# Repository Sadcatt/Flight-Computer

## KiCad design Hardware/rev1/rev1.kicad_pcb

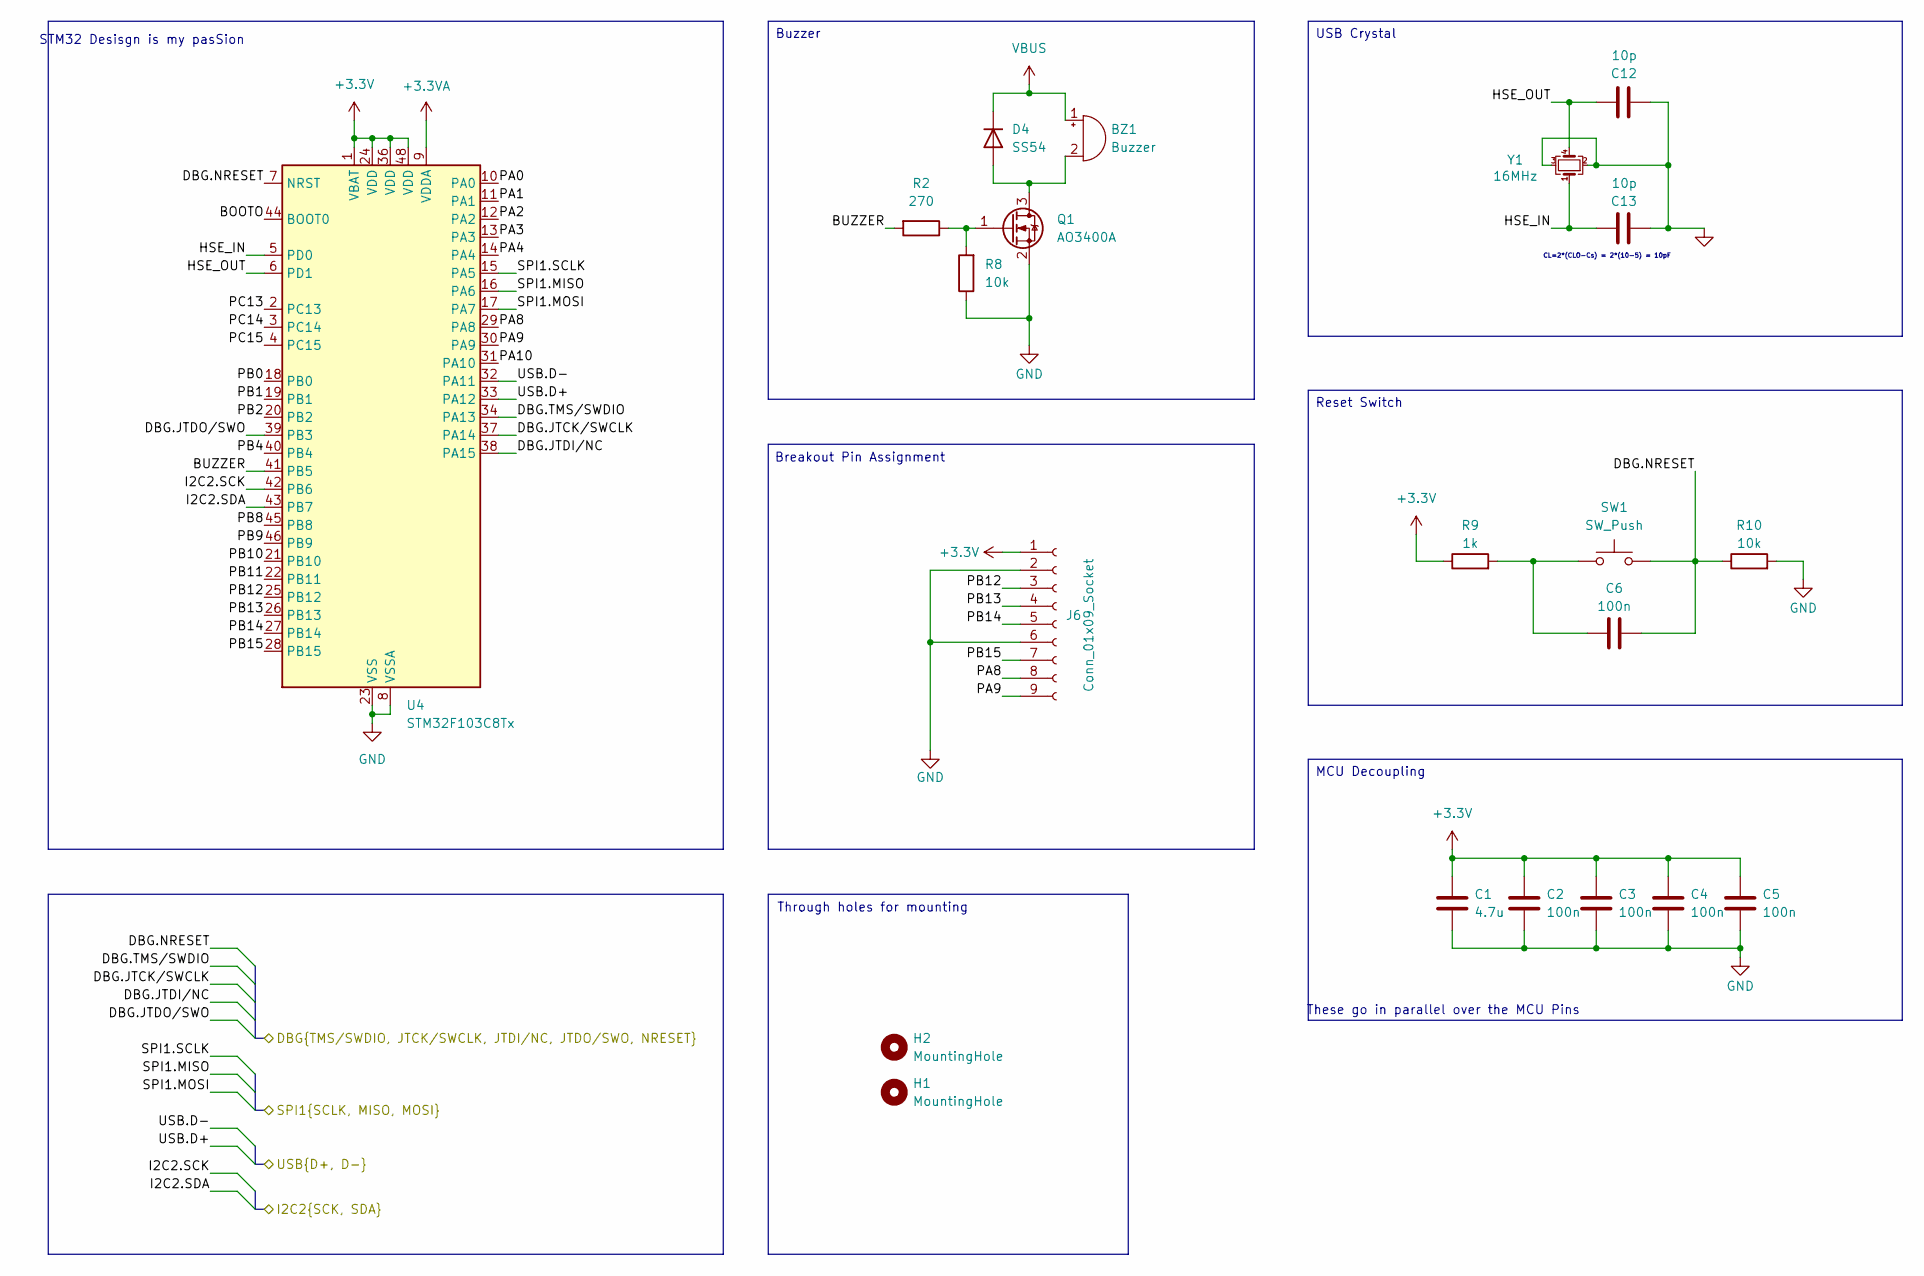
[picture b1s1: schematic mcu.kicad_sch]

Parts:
BZ1: Buzzer; MagneticBuzzer_Kingstate_KCG0601
C1: 4.7u; C_0603_1608Metric
C2, C3, C4, C5, C6: 100n; C_0402_1005Metric
C12, C13: 10p; C_0402_1005Metric
D4: SS54; D_SMA; JLCPCB Part # C22452
H1, H2: MountingHole; MountingHole_3.2mm_M3
J6: Conn_01x09_Socket; PinHeader_1x09_P1.00mm_Vertical
Q1: AO3400A; SOT-23
R2: 270; R_0603_1608Metric
R8, R10: 10k; R_0603_1608Metric
R9: 1k; R_0603_1608Metric
SW1: SW_Push; SW_Push_1P1T_XKB_TS-1187A
U4: STM32F103C8Tx; LQFP-48_7x7mm_P0.5mm
Y1: 16MHz; Crystal_SMD_3225-4Pin_3.2x2.5mm

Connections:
+3.3V: C1.1, C2.1, C3.1, C4.1, C5.1, J6.1, R9.1, U4.1 (VBAT), U4.24 (VDD), U4.36 (VDD), U4.48 (VDD); also elsewhere on the board
+3.3VA: U4.9 (VDDA); also elsewhere on the board
/Microcontroller/BOOTO: U4.44 (BOOT0)
/Microcontroller/BUZZER: R2.2, U4.41 (PB5)
/Microcontroller/DBG.JTCK/SWCLK: U4.37 (PA14); also elsewhere on the board
/Microcontroller/DBG.JTDI/NC: U4.38 (PA15); also elsewhere on the board
/Microcontroller/DBG.JTDO/SWO: U4.39 (PB3); also elsewhere on the board
/Microcontroller/DBG.NRESET: C6.2, R10.1, SW1.2, U4.7 (NRST); also elsewhere on the board
/Microcontroller/DBG.TMS/SWDIO: U4.34 (PA13); also elsewhere on the board
/Microcontroller/HSE_IN: C13.1, U4.5 (PD0), Y1.1
/Microcontroller/HSE_OUT: C12.1, U4.6 (PD1), Y1.4
/Microcontroller/I2C2.SCK: U4.42 (PB6); also elsewhere on the board
/Microcontroller/I2C2.SDA: U4.43 (PB7); also elsewhere on the board
/Microcontroller/PA0: U4.10 (PA0)
/Microcontroller/PA1: U4.11 (PA1)
/Microcontroller/PA2: U4.12 (PA2)
/Microcontroller/PA3: U4.13 (PA3)
/Microcontroller/PA4: U4.14 (PA4)
/Microcontroller/PA8: J6.8, U4.29 (PA8)
/Microcontroller/PA9: J6.9, U4.30 (PA9)
/Microcontroller/PA10: U4.31 (PA10)
/Microcontroller/PB0: U4.18 (PB0)
/Microcontroller/PB1: U4.19 (PB1)
/Microcontroller/PB2: U4.20 (PB2)
/Microcontroller/PB4: U4.40 (PB4)
/Microcontroller/PB8: U4.45 (PB8)
/Microcontroller/PB9: U4.46 (PB9)
/Microcontroller/PB10: U4.21 (PB10)
/Microcontroller/PB11: U4.22 (PB11)
/Microcontroller/PB12: J6.3, U4.25 (PB12)
/Microcontroller/PB13: J6.4, U4.26 (PB13)
/Microcontroller/PB14: J6.5, U4.27 (PB14)
/Microcontroller/PB15: J6.7, U4.28 (PB15)
/Microcontroller/PC13: U4.2 (PC13)
/Microcontroller/PC14: U4.3 (PC14)
/Microcontroller/PC15: U4.4 (PC15)
/Microcontroller/SPI1.MISO: U4.16 (PA6); also elsewhere on the board
/Microcontroller/SPI1.MOSI: U4.17 (PA7); also elsewhere on the board
/Microcontroller/SPI1.SCLK: U4.15 (PA5); also elsewhere on the board
/Microcontroller/USB.D+: U4.33 (PA12); also elsewhere on the board
/Microcontroller/USB.D-: U4.32 (PA11); also elsewhere on the board
GND: C1.2, C2.2, C3.2, C4.2, C5.2, C12.2, C13.2, J6.2, J6.6, Q1.2 (S), R8.1, R10.2, U4.8 (VSSA), U4.23 (VSS), U4.35 (VSS), U4.47 (VSS), Y1.2, Y1.3; also elsewhere on the board
unnamed: BZ1.2 (-), D4.2 (A), Q1.3 (D)
unnamed: C6.1, R9.2, SW1.1
unnamed: Q1.1 (G), R2.1, R8.2
VBUS: BZ1.1 (+), D4.1 (K); also elsewhere on the board

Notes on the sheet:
Breakout Pin Assignment
These go in parallel over the MCU Pins
CL=2*(CLO-Cs) = 2*(10-5) = 10pF
STM32 Desisgn is my pasSion
Through holes for mounting
MCU Decoupling
USB Crystal
Reset Switch
Buzzer

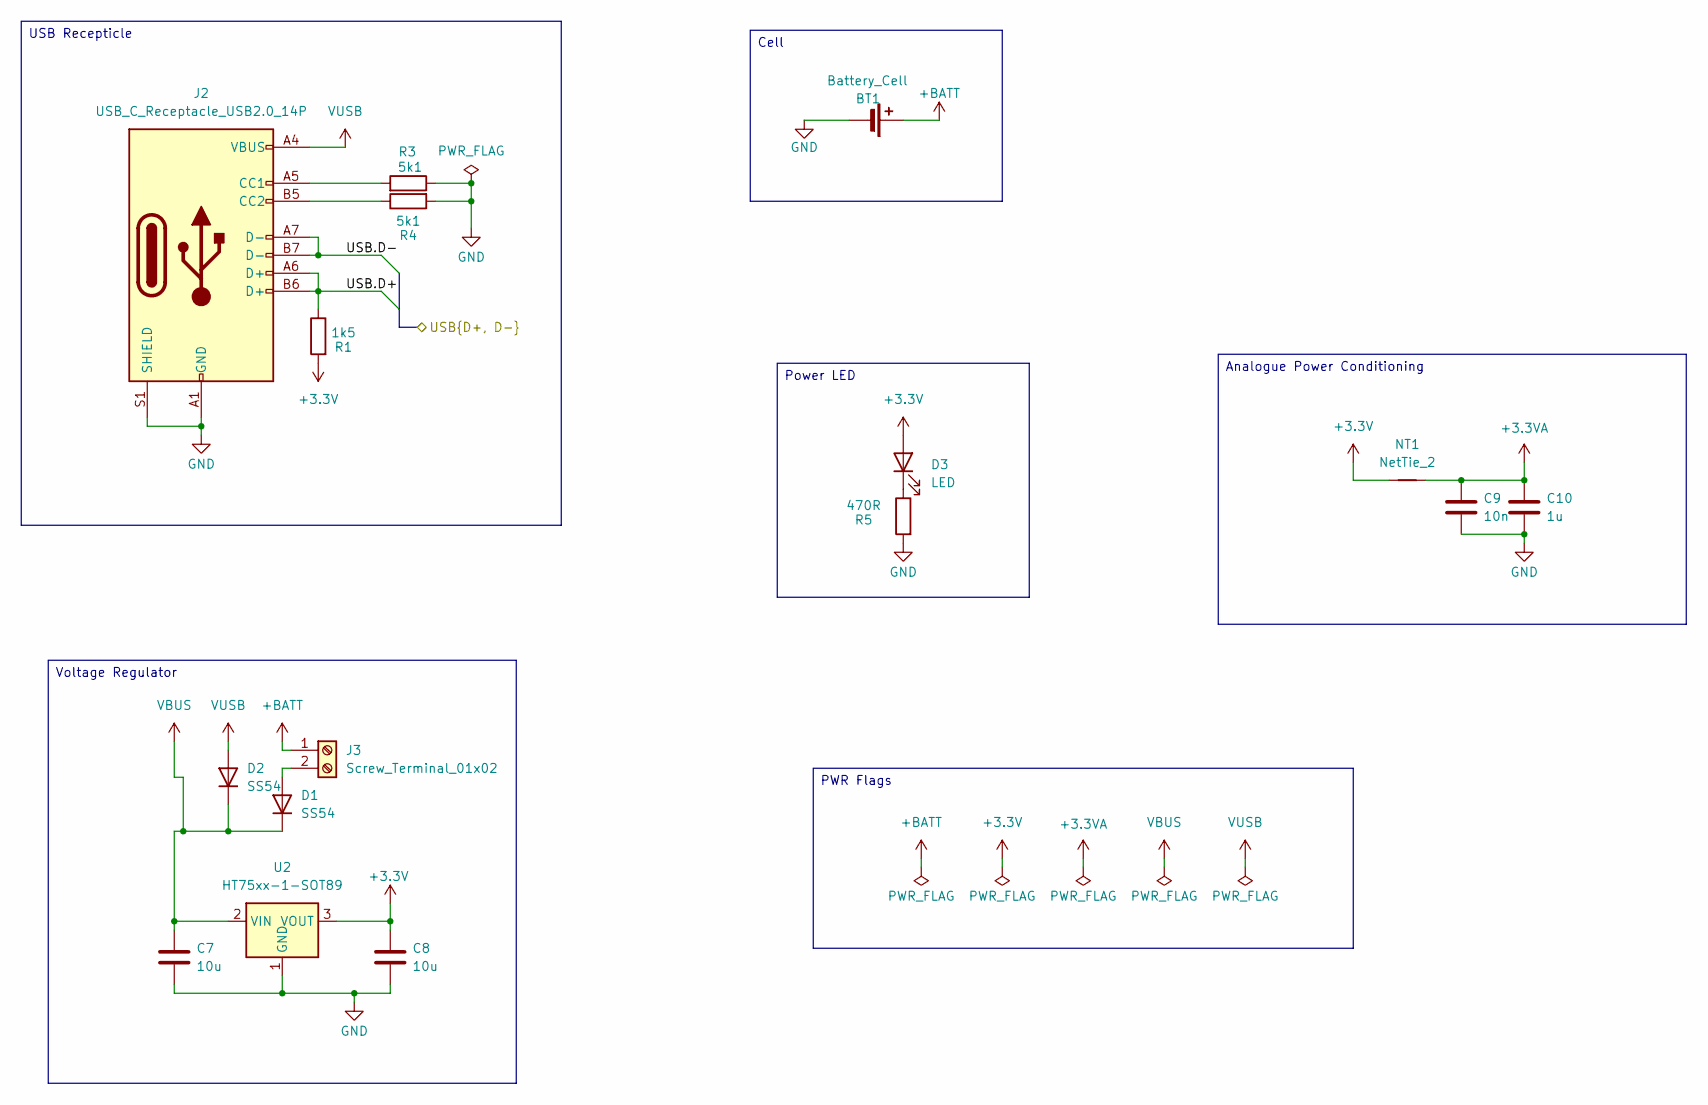
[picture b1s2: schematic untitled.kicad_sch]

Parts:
BT1: Battery_Cell; BatteryHolder_Keystone_3034_1x20mm
C7, C8: 10u; C_0603_1608Metric
C9: 10n; C_0402_1005Metric
C10: 1u; C_0603_1608Metric
D1, D2: SS54; D_SMA; JLCPCB Part # C22452
D3: LED; LED_0201_0603Metric
J2: USB_C_Receptacle_USB2.0_14P; USB_C_Receptacle_HRO_TYPE-C-31-M-12
J3: Screw_Terminal_01x02; TerminalBlock_Xinya_XY308-2.54-2P_1x02_P2.54mm_Horizontal
NT1: NetTie_2; NetTie-2_SMD_Pad0.5mm
R1: 1k5; R_0603_1608Metric
R3, R4: 5k1; R_0603_1608Metric
R5: 470R; R_0603_1608Metric
U2: HT75xx-1-SOT89; SOT-89-3

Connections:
+3.3V: C8.1, D3.2 (A), NT1.1, R1.2, U2.3 (VOUT); also elsewhere on the board
+3.3VA: C9.1, C10.1, NT1.2; also elsewhere on the board
+BATT: BT1.1 (+), J3.1
/Microcontroller/USB.D+: J2.A6 (D+), J2.B6 (D+), R1.1; also elsewhere on the board
/Microcontroller/USB.D-: J2.A7 (D-), J2.B7 (D-); also elsewhere on the board
GND: BT1.2 (-), C7.2, C8.2, C9.2, C10.2, J2.A1 (GND), J2.A12 (GND), J2.B1 (GND), J2.B12 (GND), J2.S1 (SHIELD), R3.1, R4.2, R5.2, U2.1 (GND); also elsewhere on the board
unnamed: D1.2 (A), J3.2
unnamed: D3.1 (K), R5.1
unnamed: J2.A5 (CC1), R3.2
unnamed: J2.B5 (CC2), R4.1
VBUS: C7.1, D1.1 (K), D2.1 (K), U2.2 (VIN); also elsewhere on the board
VUSB: D2.2 (A), J2.A4 (VBUS), J2.A9 (VBUS), J2.B4 (VBUS), J2.B9 (VBUS)

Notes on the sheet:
Analogue Power Conditioning
USB Recepticle
Cell
Voltage Regulator
Power LED
PWR Flags

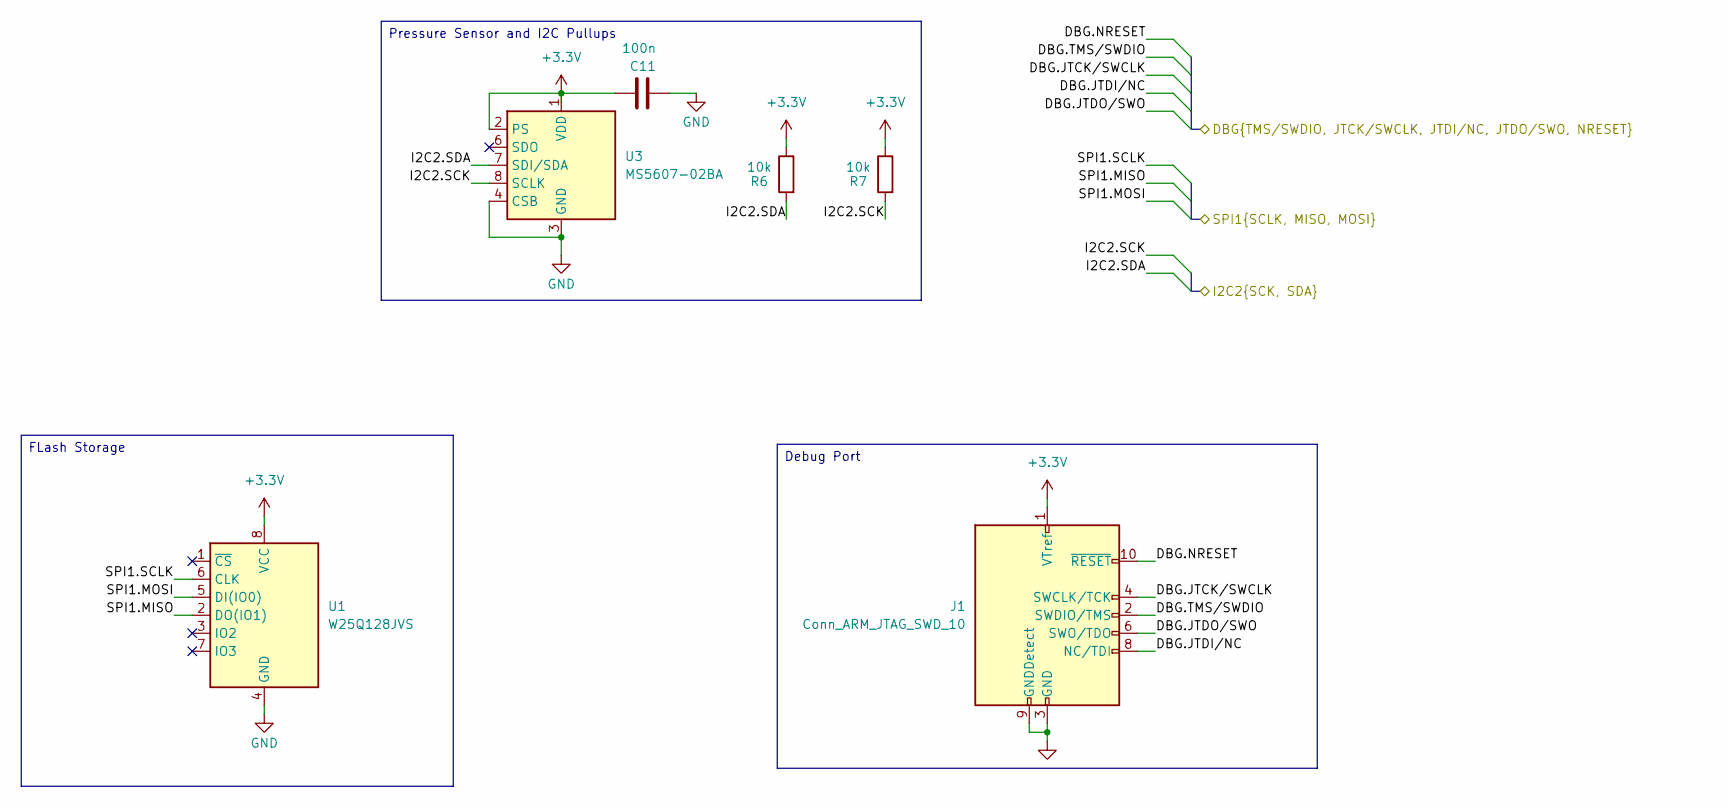
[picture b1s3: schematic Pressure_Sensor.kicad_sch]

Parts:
C11: 100n; C_0402_1005Metric
J1: Conn_ARM_JTAG_SWD_10; PinHeader_2x05_P1.27mm_Horizontal
R6, R7: 10k; R_0603_1608Metric
U1: W25Q128JVS; SOIC-8_5.23x5.23mm_P1.27mm
U3: MS5607-02BA; LGA-8_3x5mm_P1.25mm

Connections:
+3.3V: C11.1, J1.1 (VTref), R6.1, R7.1, U1.8 (VCC), U3.1 (VDD), U3.2 (PS); also elsewhere on the board
/Microcontroller/DBG.JTCK/SWCLK: J1.4 (SWCLK/TCK); also elsewhere on the board
/Microcontroller/DBG.JTDI/NC: J1.8 (NC/TDI); also elsewhere on the board
/Microcontroller/DBG.JTDO/SWO: J1.6 (SWO/TDO); also elsewhere on the board
/Microcontroller/DBG.NRESET: J1.10 (~RESET); also elsewhere on the board
/Microcontroller/DBG.TMS/SWDIO: J1.2 (SWDIO/TMS); also elsewhere on the board
/Microcontroller/I2C2.SCK: R7.2, U3.8 (SCLK); also elsewhere on the board
/Microcontroller/I2C2.SDA: R6.2, U3.7 (SDI/SDA); also elsewhere on the board
/Microcontroller/SPI1.MISO: U1.2 (DO(IO1)); also elsewhere on the board
/Microcontroller/SPI1.MOSI: U1.5 (DI(IO0)); also elsewhere on the board
/Microcontroller/SPI1.SCLK: U1.6 (CLK); also elsewhere on the board
GND: C11.2, J1.3 (GND), J1.5 (GND), J1.9 (GNDDetect), U1.4 (GND), U3.3 (GND), U3.4 (CSB), U3.5 (CSB); also elsewhere on the board

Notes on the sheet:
Debug Port
Pressure Sensor and I2C Pullups
FLash Storage

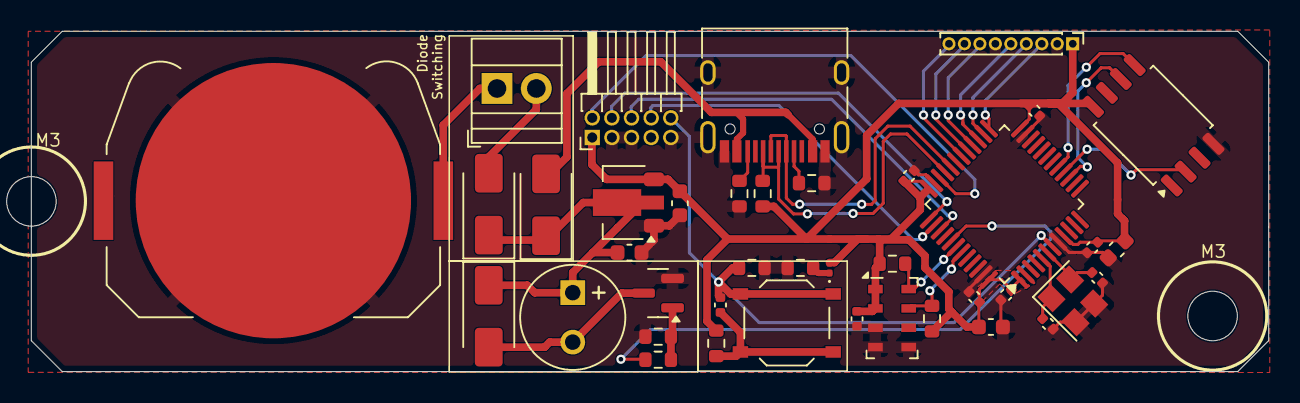
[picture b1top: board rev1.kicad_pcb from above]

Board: 4 copper layers, 80.0 x 22.0 mm, 43 parts (0 on the bottom side), 34 nets.

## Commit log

2024-09-21 Added Temp File Gitignore
2024-09-21 Added Pictures of System Diagrams
    Made in draw.io
2024-09-21 Pushed KiCad to Git
2024-09-23 hell pigeon hell pigein hell pigeon
2024-09-23 Organise files
2024-09-23 Updated System Diagram
2024-09-23 Power supply stuff
2024-10-05 Pressure sensor and debugging added
2024-10-08 Added Flash, Buzzer
2024-10-08 Some cleanup
2024-10-10 Did some stuff aye
2024-10-31 hehe did something lol
2024-11-06 who actually knows what i have done, daniel says most of it needs work lol
2024-11-07 UUUUHHH
2024-11-18 Update .gitignore
    kicad officia;l
    https://github.com/github/gitignore/blob/main/KiCad.gitignore
2024-11-24 Fixed the Errors
    The Nets i tells ya, the nets!
    need to specify the signals in the hierarchal labels
2025-01-25 i dont know what the local change is
2025-01-25 Add buses (maybe)
2025-01-28 Added Corporate Logo
2025-02-22 Removed legacy hardware from doumentation folder, updated branding images and diagrams
2025-02-22 Removed branding from main folder
2025-02-22 Removed backup files and folder as redundant on GitHub, updated hierarchical labels to include NRESET
2025-02-22 Updated footprints for capacitors
2025-02-22 Finish schematics, assign footprints
2025-02-22 Revert "Updated footprints for capacitors"
    This reverts commit 54b9e5590742c75ae1802e9536bdc0a5b115109b.
2025-02-22 Revert "Merge remote-tracking branch 'origin/dev'"
    This reverts commit 9d6b38d1428df59ab2602e839e1db75647d3fbc2, reversing
    changes made to aa461fd2fa90bcdcb689545e3dbed326723346fe.
2025-04-10 GitHub Shenanegans - Taken things from Shon's commit because easier to fix that way than to figure out how to merge properly
    Literally for the buzzer and switch, hopefully retain the capacitor fix
2025-04-10 Literal Progress
    PCB populated, schematic changed, all pins on MCU accessible from headers, all components on board, traces required
2025-04-11 Added traces ont back
    Still need to fix the header pin labels on schematic
2025-04-11 Defucked the header net assignments, cleaned up schematic sheet, routed to headers
    routing is uninformed, took care to allow ground planes to not become islands however there are some sketchy looking bits. Power still requires routing and we are really tight on space so will likely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
2025-04-20 Defenistration Comit
    Changed the crystal to be correct, still need to fix the other fixes
2025-05-14 No vallium for the whole week :(
    Net tie footprint, moved breakouts, crystal we think is close enough, tried to look for debug interface but didn't find it. no vallies :(
2025-11-14 Discarded a bunch of headers, finished traces, need stitching vias
2025-11-17 mended power trace on header
2026-06-24 Updated traces, moved mounting hole, selected switching diodes for power regulation
2026-06-25 moved some hings, need to protect the oscillator n stitch and assign parts then gem
